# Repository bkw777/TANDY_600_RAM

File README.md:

# SRAM modules for TANDY 600

There are several versions to choose from. They all work the same. Just pick whichever you like based on size, cost of parts, ease of soldering, ease of installing, etc.

[Surface-Mount single-bank 96K](#standard-version) easy to solder, polarity keyed, more expensive  
[Through-Hole single-bank 96K](#through-hole-version) same as above, plus socketable/removable chips  
[Tiny single-bank 96K](#tiny-version) more difficult to solder, miniaturized mostly just as a stunt  
[Tiny dual-bank 192K](#dual-version) most practical way to get all 192K if you can manage the soldering

## Standard Version  
<!-- [PCB from OSHPark](https://oshpark.com/shared_projects/nBVWvJ2W)  -->
[PCB for STANDARD version from PCBWAY](https://www.pcbway.com/project/shareproject/TANDY_600_RAM.html)  
[BOM for STANDARD version from DigiKey](https://www.digikey.com/short/mjtb7rnn)

<!-- [Gerbers](../../releases/latest) -->

----

## Through-Hole Version  

Same schematic as the standard version, just with all through-hole components.  
The ICs may be socketed or not as you wish. When installed in the 600 there is room for both IC's on both boards to be socketed, and the BOM includes sockets.  

[PCB for THROUGH-HOLE version from PCBWAY](https://www.pcbway.com/project/shareproject/TANDY_600_RAM_96K_THT_70a7bb4c.html)  
[BOM for THROUGH-HOLE version from DigiKey](https://www.digikey.com/short/5q7bmv0q)

----

## Tiny Version

[PCB for TINY version from PCBWAY](https://www.pcbway.com/project/shareproject/TANDY_600_RAM_TINY_Version_dedc5289.html)  
[BOM for TINY version from DigiKey](https://www.digikey.com/short/p907n2hq)

----

## DUAL VERSION

Single board that plugs into both CN1 and CN2 and supplies all 192K at once.  

<!-- [PCB from OSHPark]()  -->
[PCB for DUAL version from PCBWAY](https://www.pcbway.com/project/shareproject/TANDY_600_192K_DUAL_RAM_96d16a20.html)  
[BOM for DUAL version from DigiKey](https://www.digikey.com/short/h8bpf4wj)

----

# History / Credits

In 2017 I asked on the Tandy Color Computer Facebook group [if anyone could clone a 96K ram board for Model 600](https://www.facebook.com/groups/2359462640/permalink/10154864662292641/), and Jayeson Lee-Steere produced [Model600Sram_v1.1](https://github.com/bkw777/TANDY_600_RAM/tree/JLS-1.1) and placed it in the public domain.  

This version is different now but started from that.

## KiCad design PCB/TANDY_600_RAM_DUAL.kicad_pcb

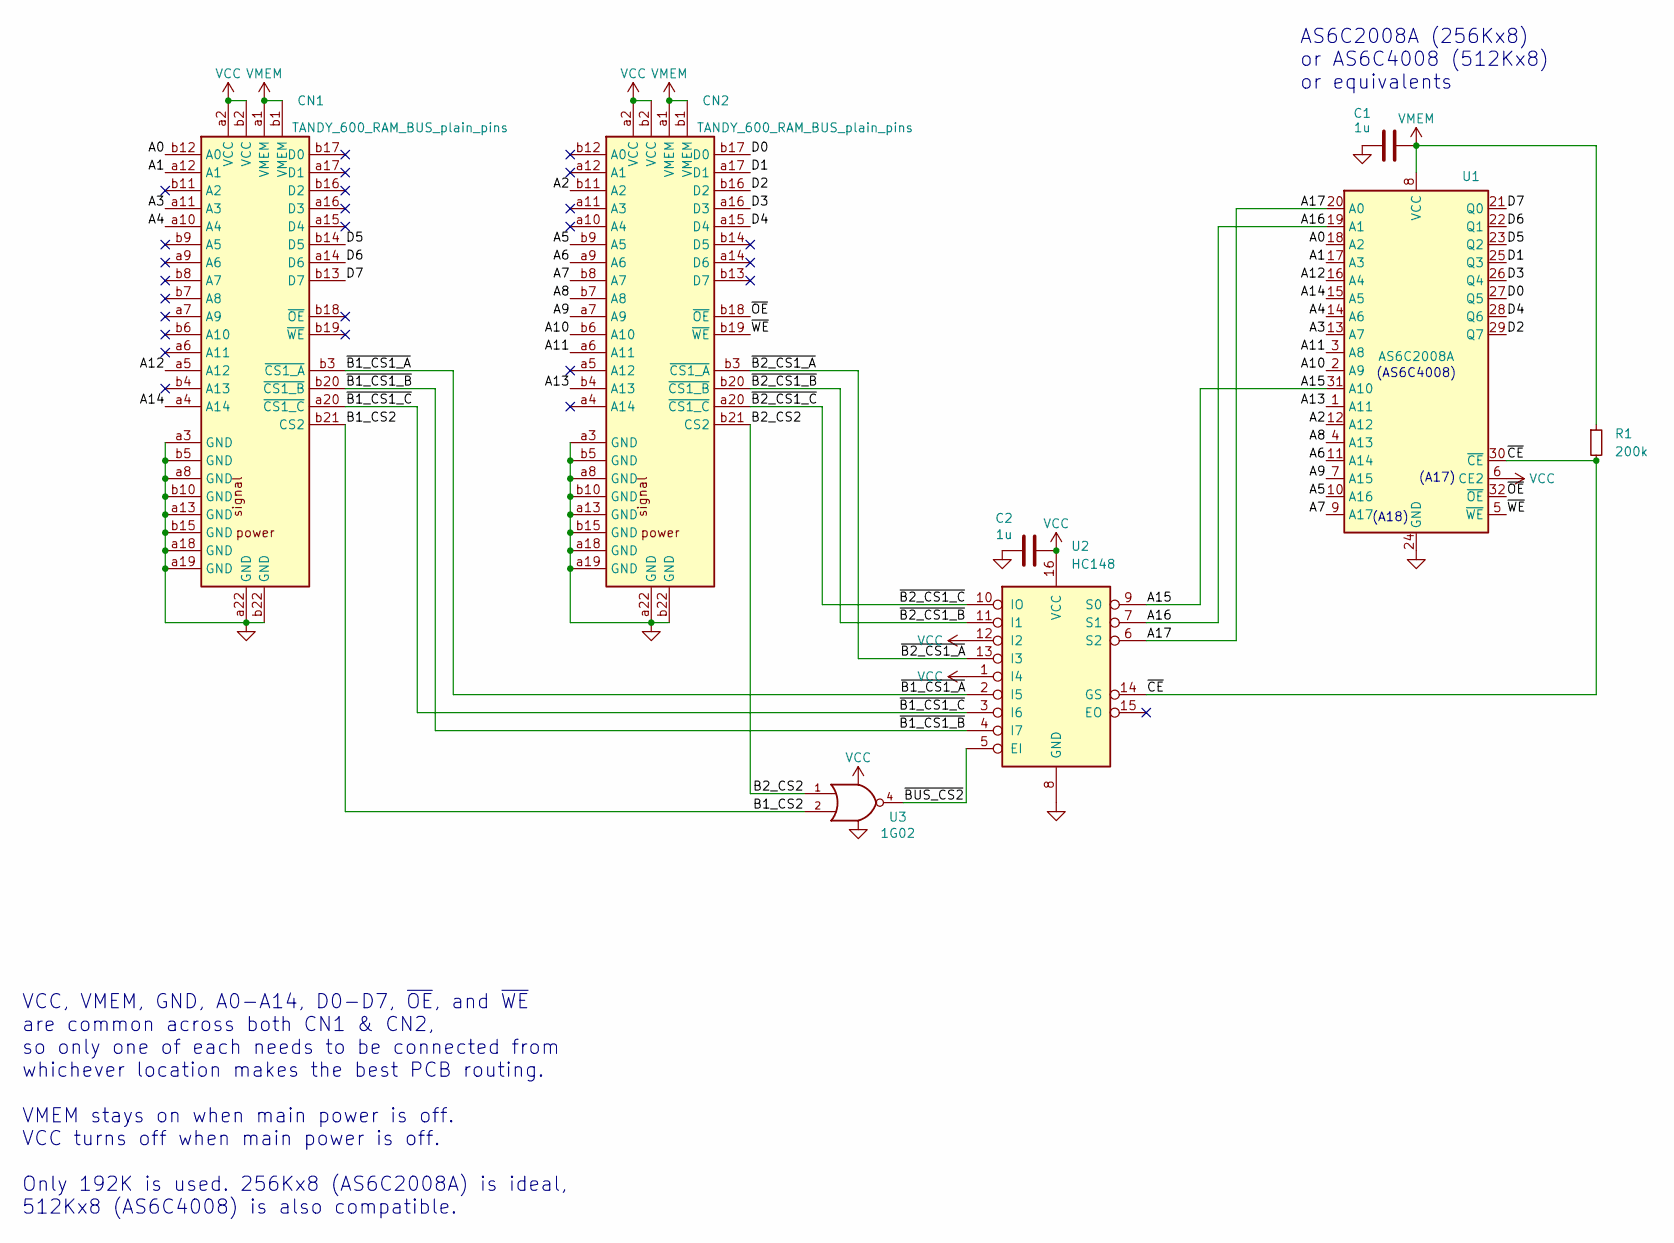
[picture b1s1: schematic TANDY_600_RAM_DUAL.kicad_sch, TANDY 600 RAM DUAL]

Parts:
C1, C2: 1u; C_0805; MPN CL21B105KAFNNNE
CN1, CN2: TANDY_600_RAM_BUS_plain_pins; DIN-41612_02x22_male_vertical_bare_pins; MPN PRPC022DAAN-RC
R1: 200k; R_0805; MPN RMCF0805FT200K
U1: AS6C2008A; TSOP32-dual; MPN AS6C4008-55STIN
U2: HC148; SOIC-16_3.9x9.9mm_P1.27mm; MPN SN74HC148DR
U3: 1G02; SOT-353_SC-70-5; MPN SN74AHC1G02DCKR

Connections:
/A0: CN1.b12 (A0), U1.18 (A2)
/A1: CN1.a12 (A1), U1.17 (A3)
/A2: CN2.b11 (A2), U1.12 (A12)
/A3: CN1.a11 (A3), U1.13 (A7)
/A4: CN1.a10 (A4), U1.14 (A6)
/A5: CN2.b9 (A5), U1.10 (A16)
/A6: CN2.a9 (A6), U1.11 (A14)
/A7: CN2.b8 (A7), U1.9 (A17)
/A8: CN2.b7 (A8), U1.4 (A13)
/A9: CN2.a7 (A9), U1.7 (A15)
/A10: CN2.b6 (A10), U1.2 (A9)
/A11: CN2.a6 (A11), U1.3 (A8)
/A12: CN1.a5 (A12), U1.16 (A4)
/A13: CN2.b4 (A13), U1.1 (A11)
/A14: CN1.a4 (A14), U1.15 (A5)
/A15: U1.31 (A10), U2.9 (S0)
/A16: U1.19 (A1), U2.7 (S1)
/A17: U1.20 (A0), U2.6 (S2)
/B1_CS2: CN1.b21 (CS2), U3.2
/B2_CS2: CN2.b21 (CS2), U3.1
/D0: CN2.b17 (D0), U1.27 (Q5)
/D1: CN2.a17 (D1), U1.25 (Q3)
/D2: CN2.b16 (D2), U1.29 (Q7)
/D3: CN2.a16 (D3), U1.26 (Q4)
/D4: CN2.a15 (D4), U1.28 (Q6)
/D5: CN1.b14 (D5), U1.23 (Q2)
/D6: CN1.a14 (D6), U1.22 (Q1)
/D7: CN1.b13 (D7), U1.21 (Q0)
/~B1_CS1_A: CN1.b3 (~CS1_A), U2.2 (I5)
/~B1_CS1_B: CN1.b20 (~CS1_B), U2.4 (I7)
/~B1_CS1_C: CN1.a20 (~CS1_C), U2.3 (I6)
/~B2_CS1_A: CN2.b3 (~CS1_A), U2.13 (I3)
/~B2_CS1_B: CN2.b20 (~CS1_B), U2.11 (I1)
/~B2_CS1_C: CN2.a20 (~CS1_C), U2.10 (IO)
/~BUS_CS2: U2.5 (EI), U3.4
/~CE: R1.2, U1.30 (~CE), U2.14 (GS)
/~OE: CN2.b18 (~OE), U1.32 (~OE)
/~WE: CN2.b19 (~WE), U1.5 (~WE)
GND: C1.2, C2.2, CN1.a3 (GND), CN1.a8 (GND), CN1.a13 (GND), CN1.a18 (GND), CN1.a19 (GND), CN1.a22 (GND), CN1.b5 (GND), CN1.b10 (GND), CN1.b15 (GND), CN1.b22 (GND), CN2.a3 (GND), CN2.a8 (GND), CN2.a13 (GND), CN2.a18 (GND), CN2.a19 (GND), CN2.a22 (GND), CN2.b5 (GND), CN2.b10 (GND), CN2.b15 (GND), CN2.b22 (GND), U1.24 (GND), U2.8 (GND), U3.3 (GND)
VCC: C2.1, CN1.a2 (VCC), CN1.b2 (VCC), CN2.a2 (VCC), CN2.b2 (VCC), U1.6 (CE2), U2.1 (I4), U2.12 (I2), U2.16 (VCC), U3.5 (VCC)
VMEM: C1.1, CN1.a1 (VMEM), CN1.b1 (VMEM), CN2.a1 (VMEM), CN2.b1 (VMEM), R1.1, U1.8 (VCC)

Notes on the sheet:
(A17)
VCC, VMEM, GND, A0-A14, D0-D7, ~{OE}, and ~{WE} are common across both CN1 & CN2, so only one of each needs to be connected from whichever location makes the best PCB routing. VMEM stays on when main power is off. VCC turns off when main power is off. Only 192K is used. 256Kx8 (AS6C2008A) is ideal,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
AS6C2008A (256Kx8) or AS6C4008 (512Kx8) or equivalents
(A18)
(AS6C4008)

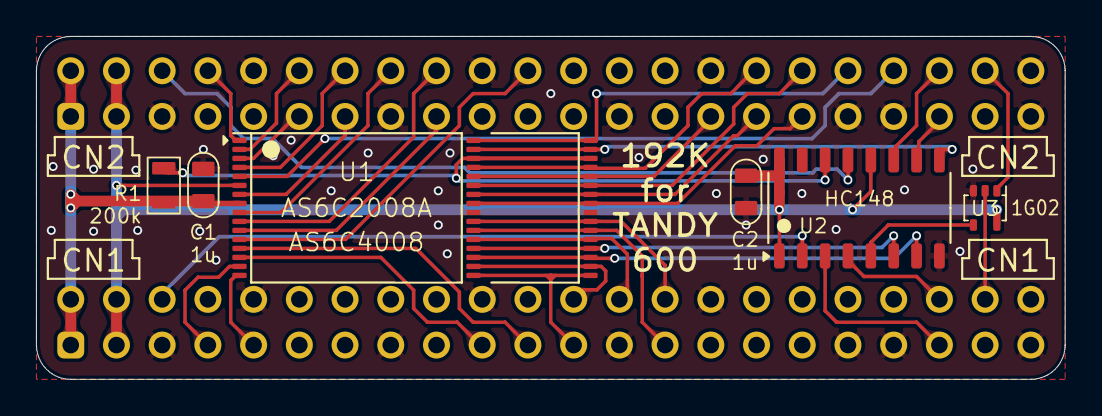
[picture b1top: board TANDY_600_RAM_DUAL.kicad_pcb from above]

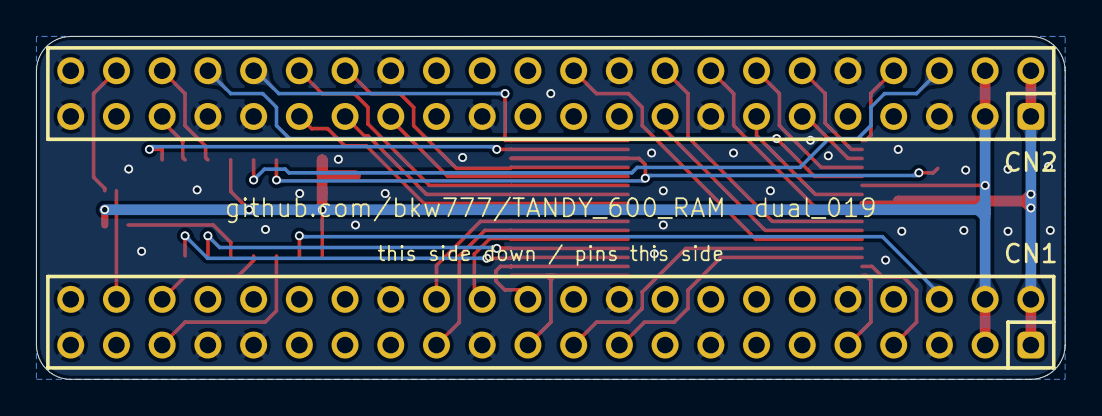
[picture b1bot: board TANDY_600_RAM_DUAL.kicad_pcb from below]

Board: 2 copper layers, 57.2 x 19.1 mm, 8 parts (2 on the bottom side), 41 nets.

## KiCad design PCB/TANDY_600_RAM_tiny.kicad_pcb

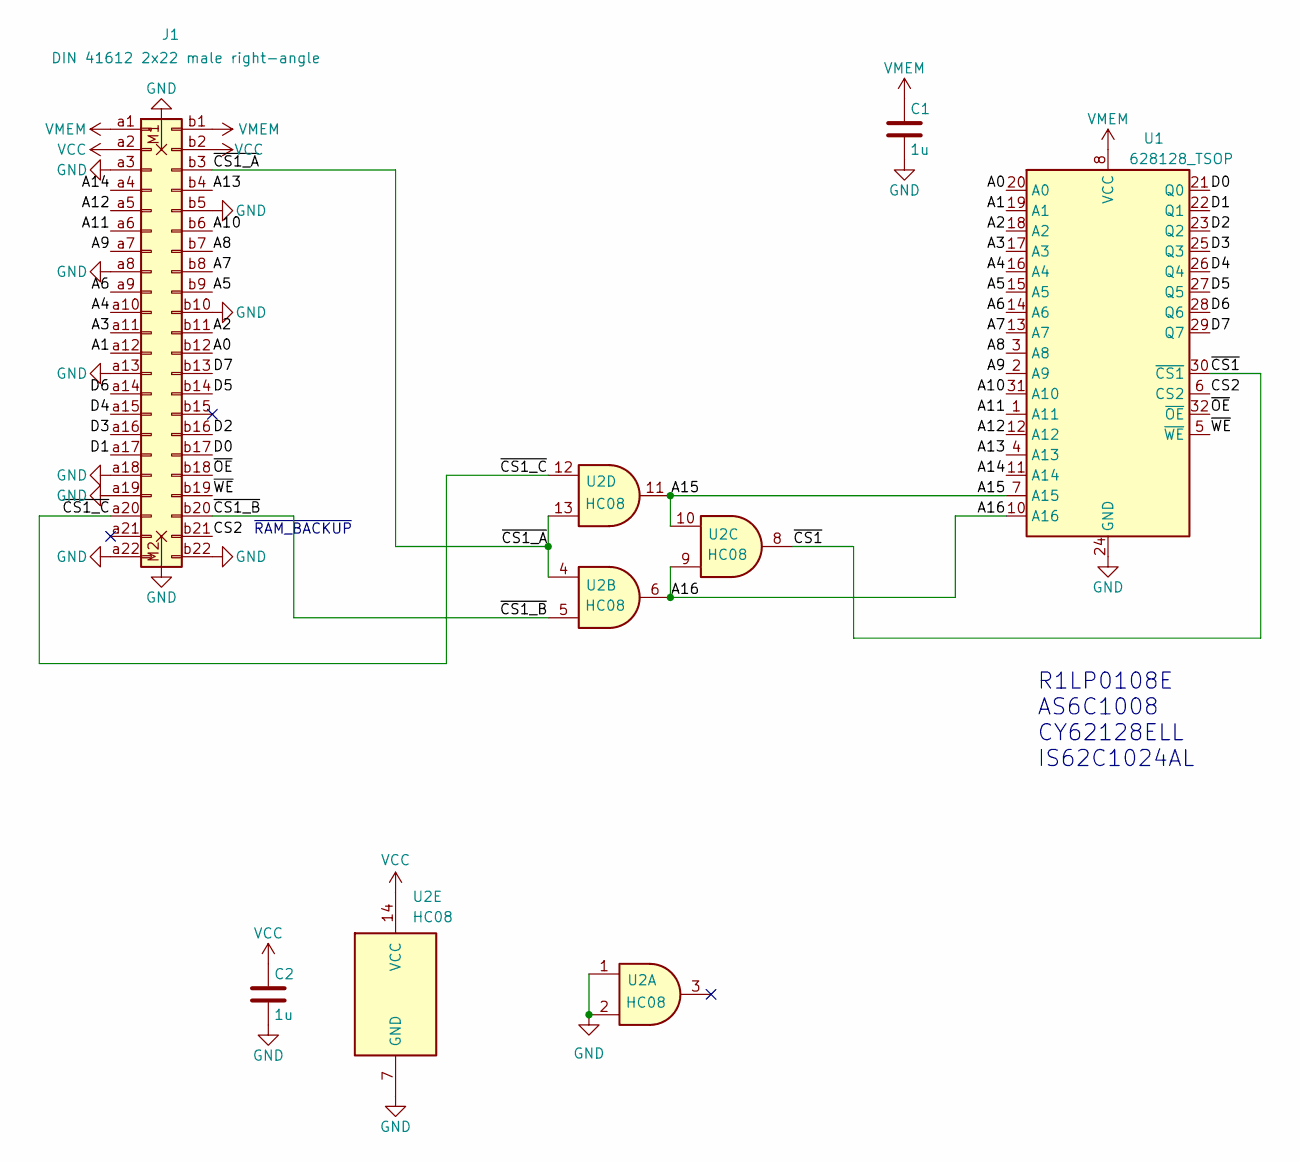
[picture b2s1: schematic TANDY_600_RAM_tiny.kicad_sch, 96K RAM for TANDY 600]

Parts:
C1, C2: 1u; C_0805
J1: DIN 41612 2x22 male right-angle; DIN-41612_02x22_male_horizontal
U1: 628128_TSOP; TSOP32-dual
U2: HC08; TSSOP-14_4.4x5mm_P0.65mm

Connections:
/A0: J1.b12, U1.20 (A0)
/A1: J1.a12, U1.19 (A1)
/A2: J1.b11, U1.18 (A2)
/A3: J1.a11, U1.17 (A3)
/A4: J1.a10, U1.16 (A4)
/A5: J1.b9, U1.15 (A5)
/A6: J1.a9, U1.14 (A6)
/A7: J1.b8, U1.13 (A7)
/A8: J1.b7, U1.3 (A8)
/A9: J1.a7, U1.2 (A9)
/A10: J1.b6, U1.31 (A10)
/A11: J1.a6, U1.1 (A11)
/A12: J1.a5, U1.12 (A12)
/A13: J1.b4, U1.4 (A13)
/A14: J1.a4, U1.11 (A14)
/A15: U1.7 (A15), U2.10, U2.11
/A16: U1.10 (A16), U2.6, U2.9
/CS2: J1.b21, U1.6 (CS2)
/D0: J1.b17, U1.21 (Q0)
/D1: J1.a17, U1.22 (Q1)
/D2: J1.b16, U1.23 (Q2)
/D3: J1.a16, U1.25 (Q3)
/D4: J1.a15, U1.26 (Q4)
/D5: J1.b14, U1.27 (Q5)
/D6: J1.a14, U1.28 (Q6)
/D7: J1.b13, U1.29 (Q7)
/~CS1_A: J1.b3, U2.4, U2.13
/~CS1_B: J1.b20, U2.5
/~CS1_C: J1.a20, U2.12
/~CS1: U1.30 (~CS1), U2.8
/~OE: J1.b18, U1.32 (~OE)
/~WE: J1.b19, U1.5 (~WE)
GND: C1.2, C2.2, J1.M1 (mount), J1.M2 (mount), J1.a3, J1.a8, J1.a13, J1.a18, J1.a19, J1.a22, J1.b5, J1.b10, J1.b22, U1.24 (GND), U2.1, U2.2, U2.7 (GND)
VCC: C2.1, J1.a2, J1.b2, U2.14 (VCC)
VMEM: C1.1, J1.a1, J1.b1, U1.8 (VCC)

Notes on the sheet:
~{RAM_BACKUP}
R1LP0108E AS6C1008 CY62128ELL IS62C1024AL

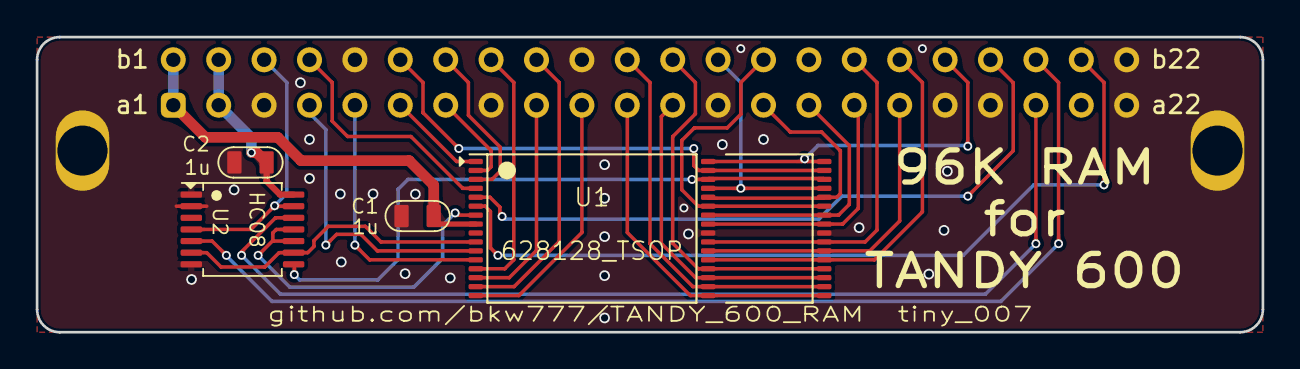
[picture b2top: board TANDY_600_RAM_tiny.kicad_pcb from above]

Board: 2 copper layers, 68.6 x 16.5 mm, 5 parts (1 on the bottom side), 35 nets.

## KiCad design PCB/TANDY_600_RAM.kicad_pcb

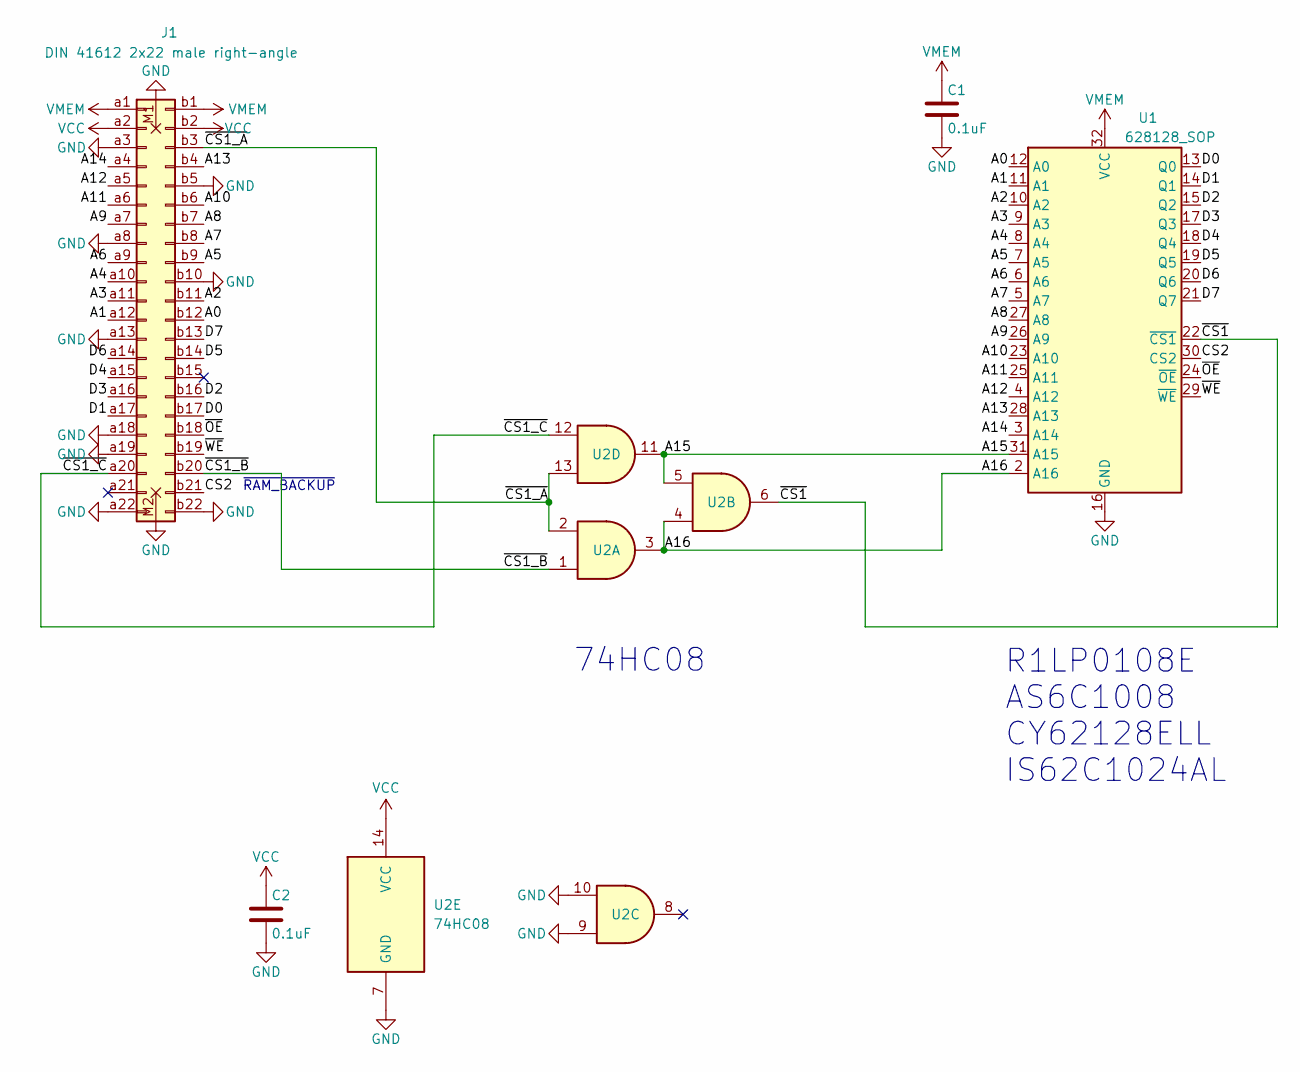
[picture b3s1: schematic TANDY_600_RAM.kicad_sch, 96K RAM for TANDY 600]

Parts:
C1, C2: 0.1uF; C_1206
J1: DIN 41612 2x22 male right-angle; DIN-41612_02x22_male_horizontal
U1: 628128_SOP; SOP-32W
U2: 74HC08; SOIC-14_3.9x8.7mm_P1.27mm

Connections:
/A0: J1.b12, U1.12 (A0)
/A1: J1.a12, U1.11 (A1)
/A2: J1.b11, U1.10 (A2)
/A3: J1.a11, U1.9 (A3)
/A4: J1.a10, U1.8 (A4)
/A5: J1.b9, U1.7 (A5)
/A6: J1.a9, U1.6 (A6)
/A7: J1.b8, U1.5 (A7)
/A8: J1.b7, U1.27 (A8)
/A9: J1.a7, U1.26 (A9)
/A10: J1.b6, U1.23 (A10)
/A11: J1.a6, U1.25 (A11)
/A12: J1.a5, U1.4 (A12)
/A13: J1.b4, U1.28 (A13)
/A14: J1.a4, U1.3 (A14)
/A15: U1.31 (A15), U2.5, U2.11
/A16: U1.2 (A16), U2.3, U2.4
/CS2: J1.b21, U1.30 (CS2)
/D0: J1.b17, U1.13 (Q0)
/D1: J1.a17, U1.14 (Q1)
/D2: J1.b16, U1.15 (Q2)
/D3: J1.a16, U1.17 (Q3)
/D4: J1.a15, U1.18 (Q4)
/D5: J1.b14, U1.19 (Q5)
/D6: J1.a14, U1.20 (Q6)
/D7: J1.b13, U1.21 (Q7)
/~CS1_A: J1.b3, U2.2, U2.13
/~CS1_B: J1.b20, U2.1
/~CS1_C: J1.a20, U2.12
/~CS1: U1.22 (~CS1), U2.6
/~OE: J1.b18, U1.24 (~OE)
/~WE: J1.b19, U1.29 (~WE)
GND: C1.2, C2.2, J1.M1 (mount), J1.M2 (mount), J1.a3, J1.a8, J1.a13, J1.a18, J1.a19, J1.a22, J1.b5, J1.b10, J1.b22, U1.16 (GND), U2.7 (GND), U2.9, U2.10
VCC: C2.1, J1.a2, J1.b2, U2.14 (VCC)
VMEM: C1.1, J1.a1, J1.b1, U1.32 (VCC)

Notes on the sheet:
~{RAM_BACKUP}
R1LP0108E AS6C1008 CY62128ELL IS62C1024AL
74HC08

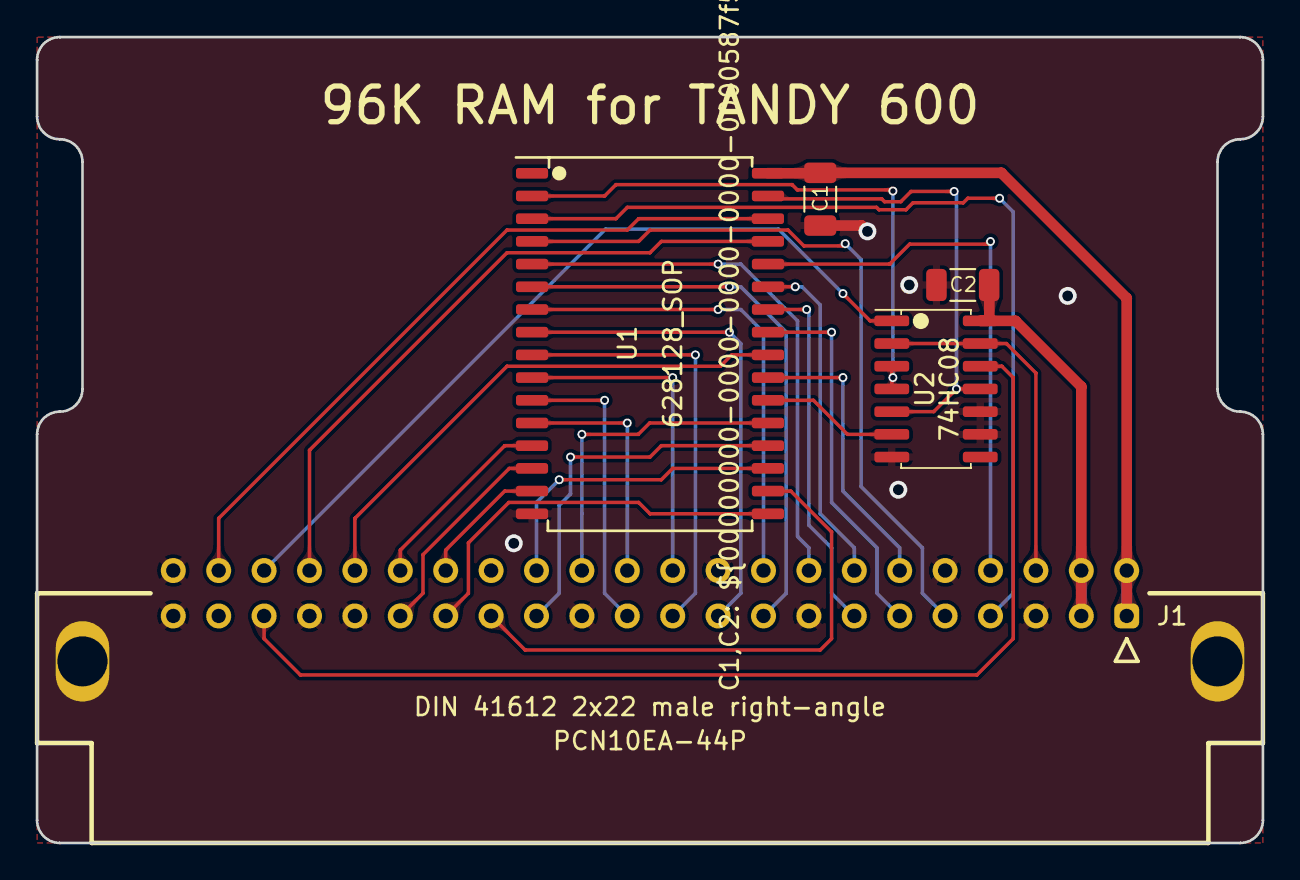
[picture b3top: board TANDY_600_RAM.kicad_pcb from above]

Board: 2 copper layers, 68.6 x 45.1 mm, 5 parts (0 on the bottom side), 35 nets.

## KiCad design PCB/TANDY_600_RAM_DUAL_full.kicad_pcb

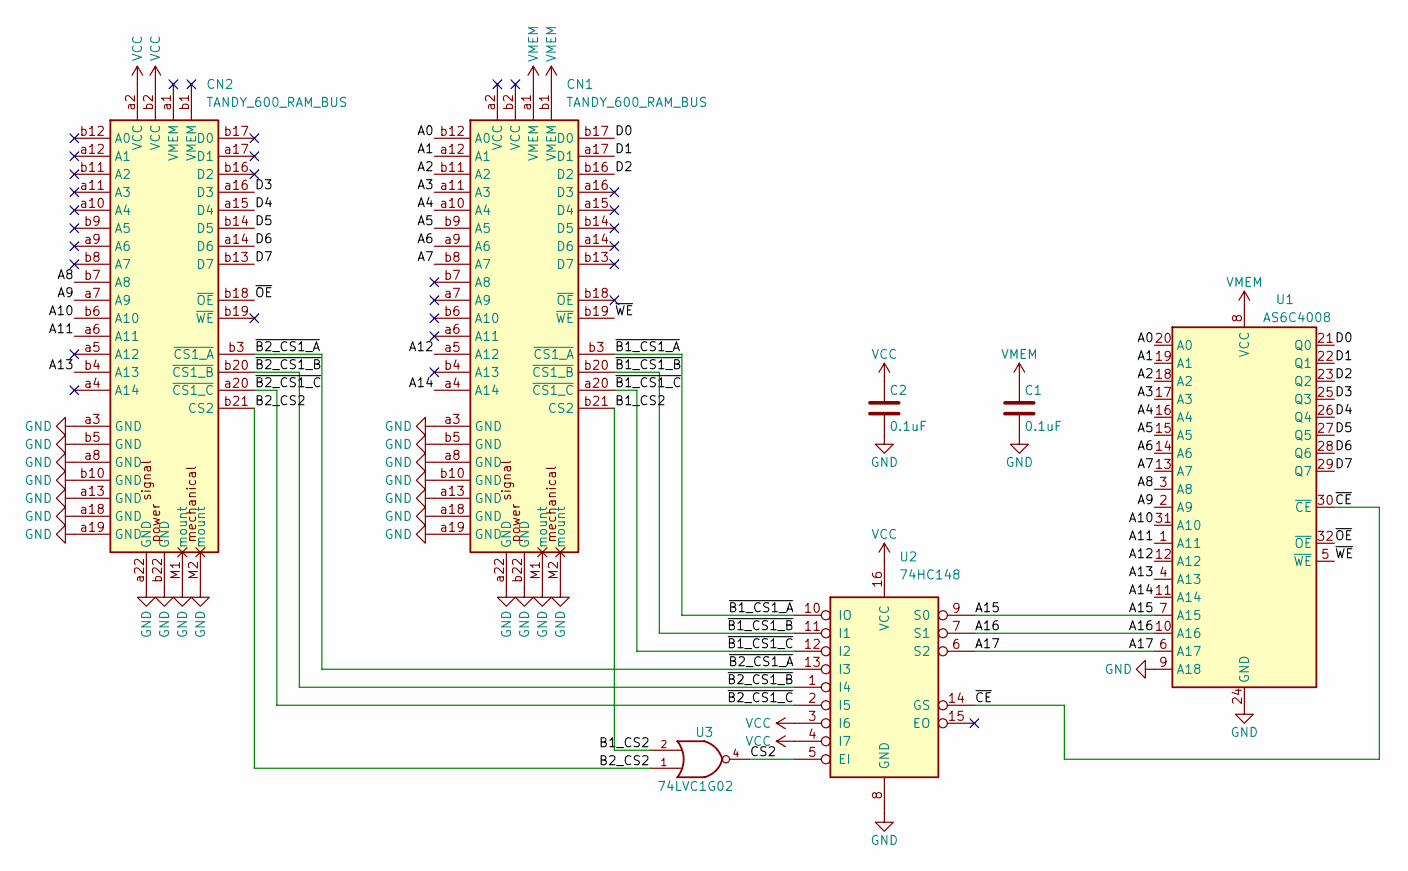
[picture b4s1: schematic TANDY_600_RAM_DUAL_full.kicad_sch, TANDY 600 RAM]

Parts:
C1, C2: 0.1uF; C_0805
CN1, CN2: TANDY_600_RAM_BUS; DIN-41612_02x22_male_vertical
U1: AS6C4008; TSOP32-dual
U2: 74HC148; SOIC-16_4x10
U3: 74LVC1G02; SOT-353_SC-70-5

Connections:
/A0: CN1.b12 (A0), U1.20 (A0)
/A1: CN1.a12 (A1), U1.19 (A1)
/A2: CN1.b11 (A2), U1.18 (A2)
/A3: CN1.a11 (A3), U1.17 (A3)
/A4: CN1.a10 (A4), U1.16 (A4)
/A5: CN1.b9 (A5), U1.15 (A5)
/A6: CN1.a9 (A6), U1.14 (A6)
/A7: CN1.b8 (A7), U1.13 (A7)
/A8: CN2.b7 (A8), U1.3 (A8)
/A9: CN2.a7 (A9), U1.2 (A9)
/A10: CN2.b6 (A10), U1.31 (A10)
/A11: CN2.a6 (A11), U1.1 (A11)
/A12: CN1.a5 (A12), U1.12 (A12)
/A13: CN2.b4 (A13), U1.4 (A13)
/A14: CN1.a4 (A14), U1.11 (A14)
/A15: U1.7 (A15), U2.9 (S0)
/A16: U1.10 (A16), U2.7 (S1)
/A17: U1.6 (A17), U2.6 (S2)
/B1_CS2: CN1.b21 (CS2), U3.2
/B2_CS2: CN2.b21 (CS2), U3.1
/CS2: U2.5 (EI), U3.4
/D0: CN1.b17 (D0), U1.21 (Q0)
/D1: CN1.a17 (D1), U1.22 (Q1)
/D2: CN1.b16 (D2), U1.23 (Q2)
/D3: CN2.a16 (D3), U1.25 (Q3)
/D4: CN2.a15 (D4), U1.26 (Q4)
/D5: CN2.b14 (D5), U1.27 (Q5)
/D6: CN2.a14 (D6), U1.28 (Q6)
/D7: CN2.b13 (D7), U1.29 (Q7)
/~B1_CS1_A: CN1.b3 (~CS1_A), U2.10 (IO)
/~B1_CS1_B: CN1.b20 (~CS1_B), U2.11 (I1)
/~B1_CS1_C: CN1.a20 (~CS1_C), U2.12 (I2)
/~B2_CS1_A: CN2.b3 (~CS1_A), U2.13 (I3)
/~B2_CS1_B: CN2.b20 (~CS1_B), U2.1 (I4)
/~B2_CS1_C: CN2.a20 (~CS1_C), U2.2 (I5)
/~CE: U1.30 (~CE), U2.14 (GS)
/~OE: CN2.b18 (~OE), U1.32 (~OE)
/~WE: CN1.b19 (~WE), U1.5 (~WE)
GND: C1.2, C2.2, CN1.M1 (mount), CN1.M2 (mount), CN1.a3 (GND), CN1.a8 (GND), CN1.a13 (GND), CN1.a18 (GND), CN1.a19 (GND), CN1.a22 (GND), CN1.b5 (GND), CN1.b10 (GND), CN1.b22 (GND), CN2.M1 (mount), CN2.M2 (mount), CN2.a3 (GND), CN2.a8 (GND), CN2.a13 (GND), CN2.a18 (GND), CN2.a19 (GND), CN2.a22 (GND), CN2.b5 (GND), CN2.b10 (GND), CN2.b22 (GND), U1.9 (A18), U1.24 (GND), U2.8 (GND), U3.3 (GND)
VCC: C2.1, CN2.a2 (VCC), CN2.b2 (VCC), U2.3 (I6), U2.4 (I7), U2.16 (VCC), U3.5 (VCC)
VMEM: C1.1, CN1.a1 (VMEM), CN1.b1 (VMEM), U1.8 (VCC)

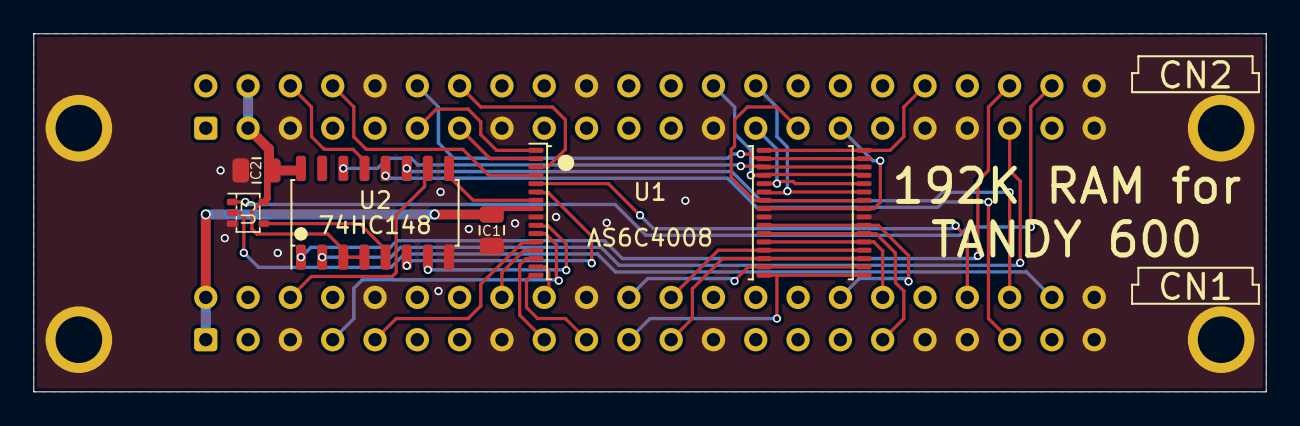
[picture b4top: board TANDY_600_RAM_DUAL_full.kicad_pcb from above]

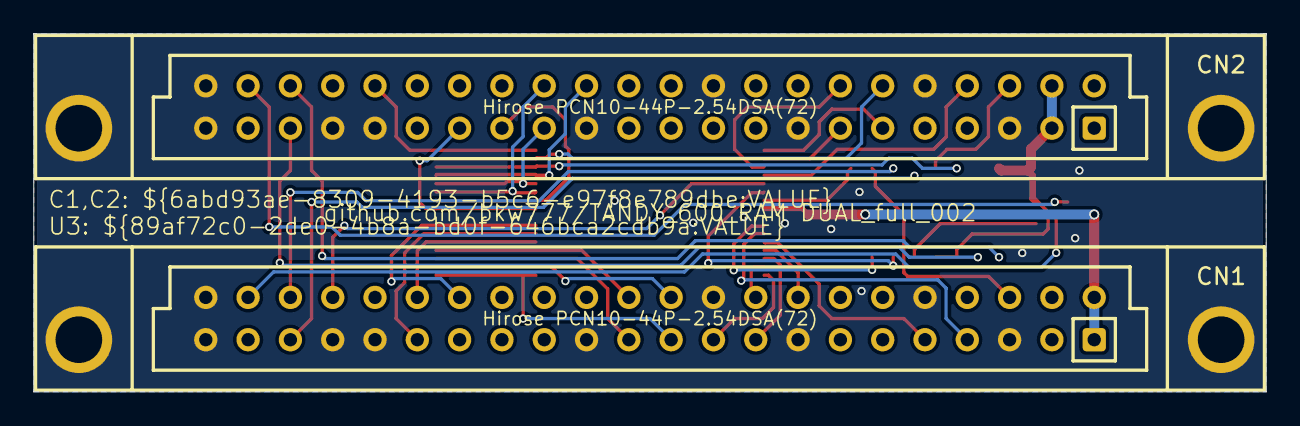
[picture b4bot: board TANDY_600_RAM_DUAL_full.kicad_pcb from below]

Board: 2 copper layers, 74.0 x 21.5 mm, 7 parts (2 on the bottom side), 41 nets.

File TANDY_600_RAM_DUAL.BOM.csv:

"Index","Quantity","Part Number","Manufacturer Part Number","Description","Customer Reference","Available","Backorder","Unit Price","Extended Price USD"
"1","1","296-26468-1-ND","SN74HC148DR","IC PRIORITY ENCOD 1 X 8:3 16SOIC","","1","0","0.44000","0.44"
"2","1","1450-1029-ND","AS6C4008-55STIN","IC SRAM 4MBIT PARALLEL 32STSOP","","1","0","5.16000","5.16"
"3","1","1727-6062-1-ND","74LVC1G02GW,125","IC GATE NOR 1CH 2-INP 5TSSOP","","1","0","0.38000","0.38"
"4","2","478-12795-1-ND","KGM21NR71C104MT","CAP CER 0.1UF 16V X7R 0805","","2","0","0.23000","0.46"
"5","2","S2011EC-22-ND","PRPC022DAAN-RC","CONN HEADER VERT 44POS 2.54MM","","2","0","0.82000","1.64"
"6","1","RMCF0805JT200KCT-ND","RMCF0805JT200K","RES 200K OHM 5% 1/8W 0805","","1","0","0.10000","0.10"

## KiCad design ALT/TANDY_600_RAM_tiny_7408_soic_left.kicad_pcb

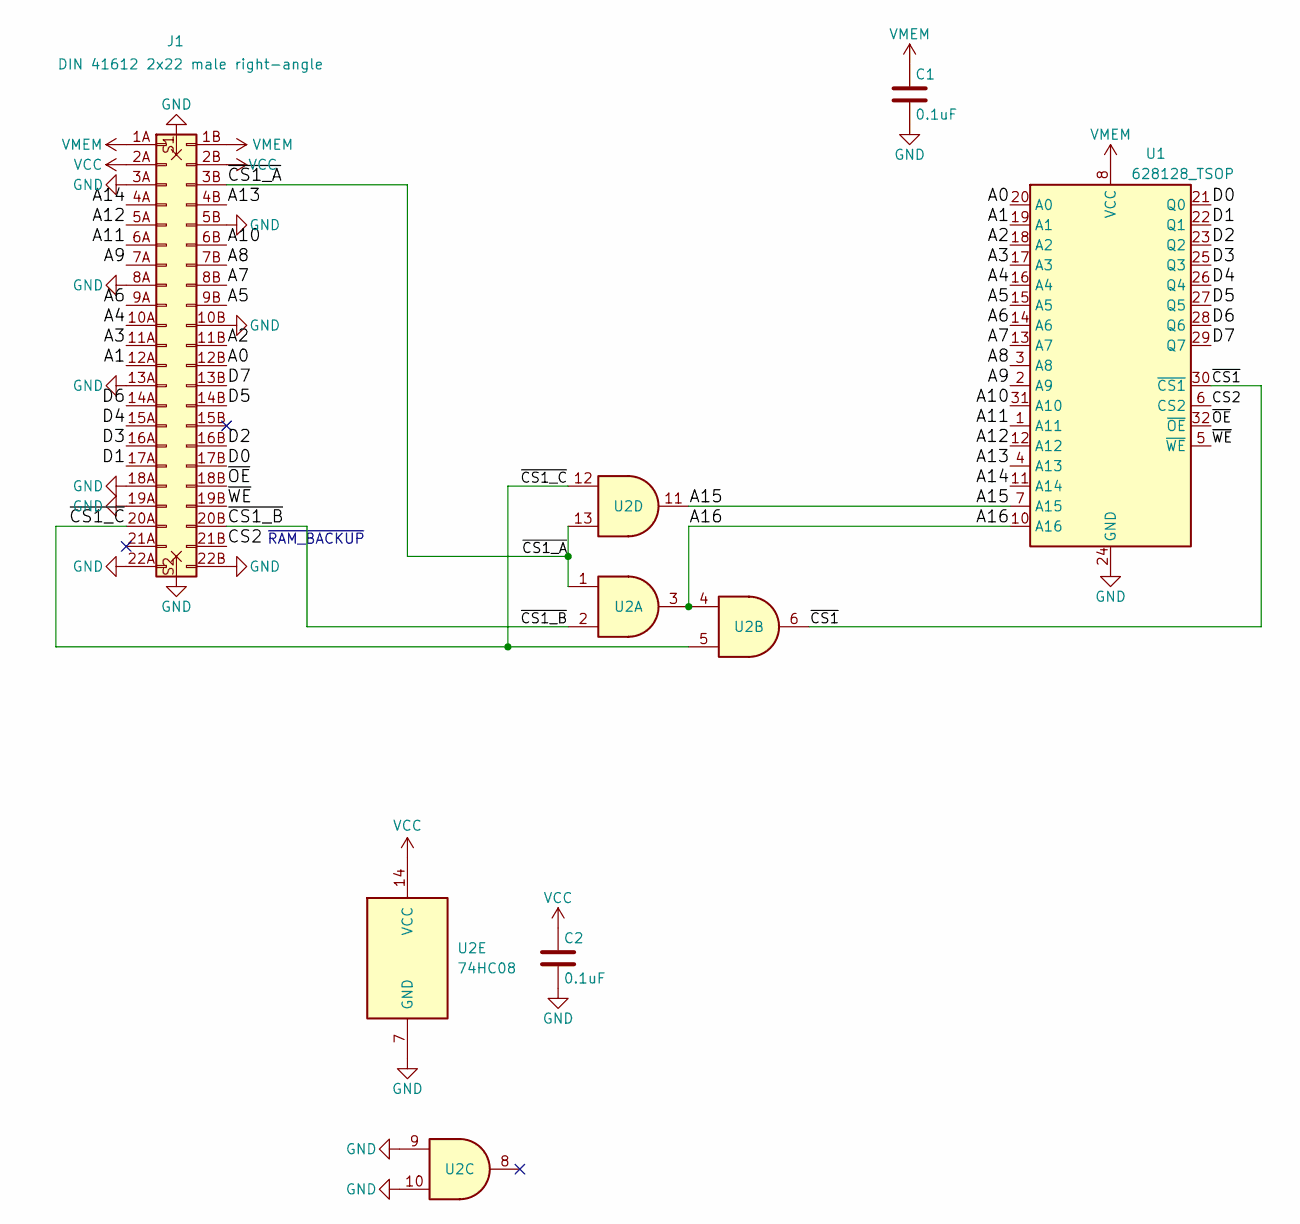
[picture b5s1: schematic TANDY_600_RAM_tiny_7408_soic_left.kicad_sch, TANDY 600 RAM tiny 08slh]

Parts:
C1, C2: 0.1uF; C_0805
J1: DIN 41612 2x22 male right-angle
U1: 628128_TSOP; TSOP32-dual
U2: 74HC08; SOIC-14_3.9x8.7mm_P1.27mm

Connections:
/A0: J1.12B, U1.20 (A0)
/A1: J1.12A, U1.19 (A1)
/A2: J1.11B, U1.18 (A2)
/A3: J1.11A, U1.17 (A3)
/A4: J1.10A, U1.16 (A4)
/A5: J1.9B, U1.15 (A5)
/A6: J1.9A, U1.14 (A6)
/A7: J1.8B, U1.13 (A7)
/A8: J1.7B, U1.3 (A8)
/A9: J1.7A, U1.2 (A9)
/A10: J1.6B, U1.31 (A10)
/A11: J1.6A, U1.1 (A11)
/A12: J1.5A, U1.12 (A12)
/A13: J1.4B, U1.4 (A13)
/A14: J1.4A, U1.11 (A14)
/A15: U1.7 (A15), U2.11
/A16: U1.10 (A16), U2.3, U2.4
/CS2: J1.21B, U1.6 (CS2)
/D0: J1.17B, U1.21 (Q0)
/D1: J1.17A, U1.22 (Q1)
/D2: J1.16B, U1.23 (Q2)
/D3: J1.16A, U1.25 (Q3)
/D4: J1.15A, U1.26 (Q4)
/D5: J1.14B, U1.27 (Q5)
/D6: J1.14A, U1.28 (Q6)
/D7: J1.13B, U1.29 (Q7)
/~CS1_A: J1.3B, U2.1, U2.13
/~CS1_B: J1.20B, U2.2
/~CS1_C: J1.20A, U2.5, U2.12
/~CS1: U1.30 (~CS1), U2.6
/~OE: J1.18B, U1.32 (~OE)
/~WE: J1.19B, U1.5 (~WE)
GND: C1.2, C2.2, J1.3A, J1.5B, J1.8A, J1.10B, J1.13A, J1.18A, J1.19A, J1.22A, J1.22B, J1.S1 (mount), J1.S2 (mount), U1.24 (GND), U2.7 (GND), U2.9, U2.10
VCC: C2.1, J1.2A, J1.2B, U2.14 (VCC)
VMEM: C1.1, J1.1A, J1.1B, U1.8 (VCC)

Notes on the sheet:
~{RAM_BACKUP}

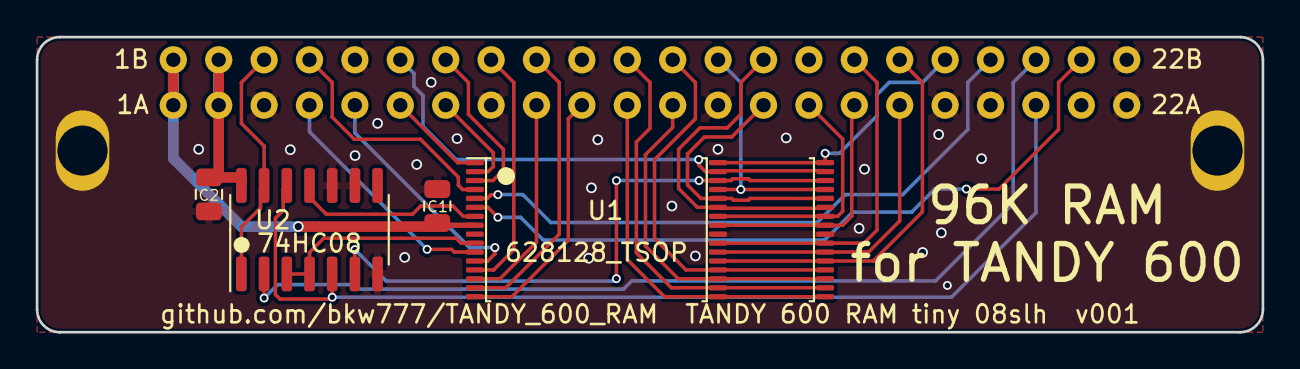
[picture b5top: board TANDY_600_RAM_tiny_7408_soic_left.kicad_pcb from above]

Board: 2 copper layers, 68.6 x 16.5 mm, 5 parts (1 on the bottom side), 35 nets.

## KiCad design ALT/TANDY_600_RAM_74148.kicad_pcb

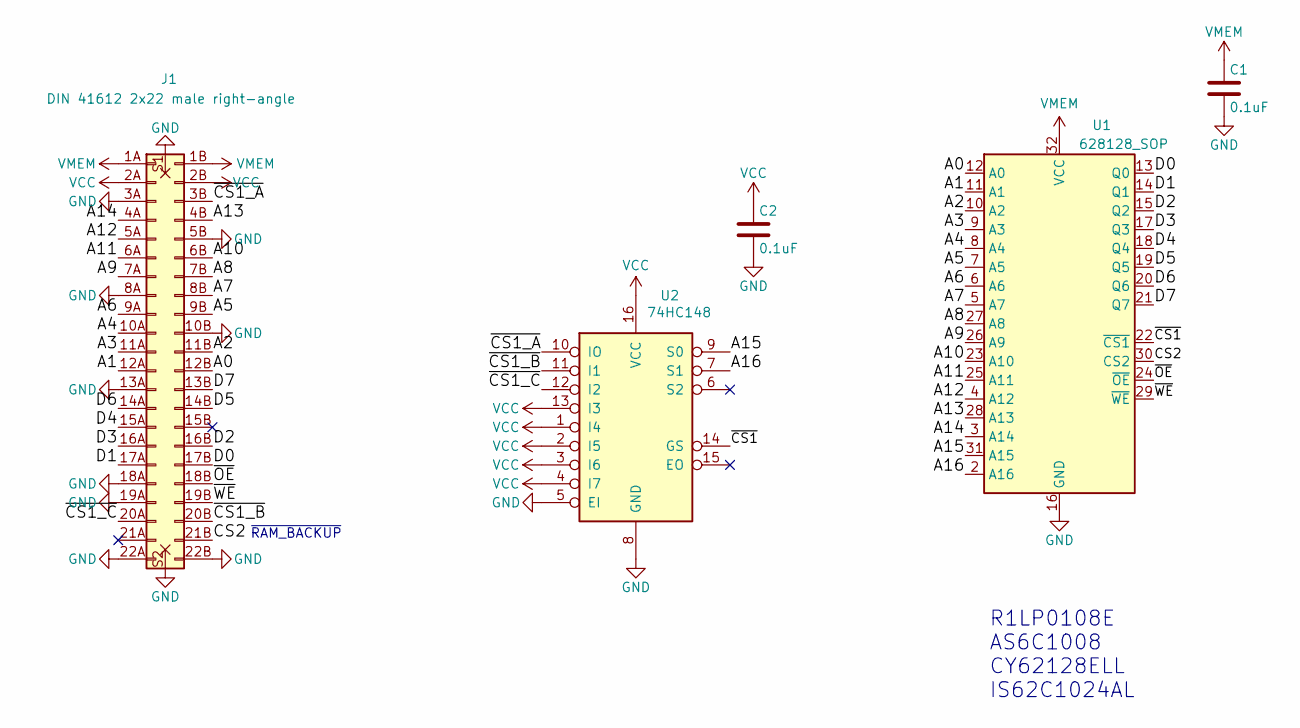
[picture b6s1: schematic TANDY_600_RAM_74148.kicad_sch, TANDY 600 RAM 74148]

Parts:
C1, C2: 0.1uF; C_1206
J1: DIN 41612 2x22 male right-angle
U1: 628128_SOP; SOP-32W
U2: 74HC148; SOIC-SOP-16

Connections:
/A0: J1.12B, U1.12 (A0)
/A1: J1.12A, U1.11 (A1)
/A2: J1.11B, U1.10 (A2)
/A3: J1.11A, U1.9 (A3)
/A4: J1.10A, U1.8 (A4)
/A5: J1.9B, U1.7 (A5)
/A6: J1.9A, U1.6 (A6)
/A7: J1.8B, U1.5 (A7)
/A8: J1.7B, U1.27 (A8)
/A9: J1.7A, U1.26 (A9)
/A10: J1.6B, U1.23 (A10)
/A11: J1.6A, U1.25 (A11)
/A12: J1.5A, U1.4 (A12)
/A13: J1.4B, U1.28 (A13)
/A14: J1.4A, U1.3 (A14)
/A15: U1.31 (A15), U2.9 (S0)
/A16: U1.2 (A16), U2.7 (S1)
/CS2: J1.21B, U1.30 (CS2)
/D0: J1.17B, U1.13 (Q0)
/D1: J1.17A, U1.14 (Q1)
/D2: J1.16B, U1.15 (Q2)
/D3: J1.16A, U1.17 (Q3)
/D4: J1.15A, U1.18 (Q4)
/D5: J1.14B, U1.19 (Q5)
/D6: J1.14A, U1.20 (Q6)
/D7: J1.13B, U1.21 (Q7)
/~CS1_A: J1.3B, U2.10 (IO)
/~CS1_B: J1.20B, U2.11 (I1)
/~CS1_C: J1.20A, U2.12 (I2)
/~CS1: U1.22 (~CS1), U2.14 (GS)
/~OE: J1.18B, U1.24 (~OE)
/~WE: J1.19B, U1.29 (~WE)
GND: C1.2, C2.2, J1.3A, J1.5B, J1.8A, J1.10B, J1.13A, J1.18A, J1.19A, J1.22A, J1.22B, J1.S1 (mount), J1.S2 (mount), U1.16 (GND), U2.5 (EI), U2.8 (GND)
VCC: C2.1, J1.2A, J1.2B, U2.1 (I4), U2.2 (I5), U2.3 (I6), U2.4 (I7), U2.13 (I3), U2.16 (VCC)
VMEM: C1.1, J1.1A, J1.1B, U1.32 (VCC)

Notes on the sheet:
~{RAM_BACKUP}
R1LP0108E AS6C1008 CY62128ELL IS62C1024AL

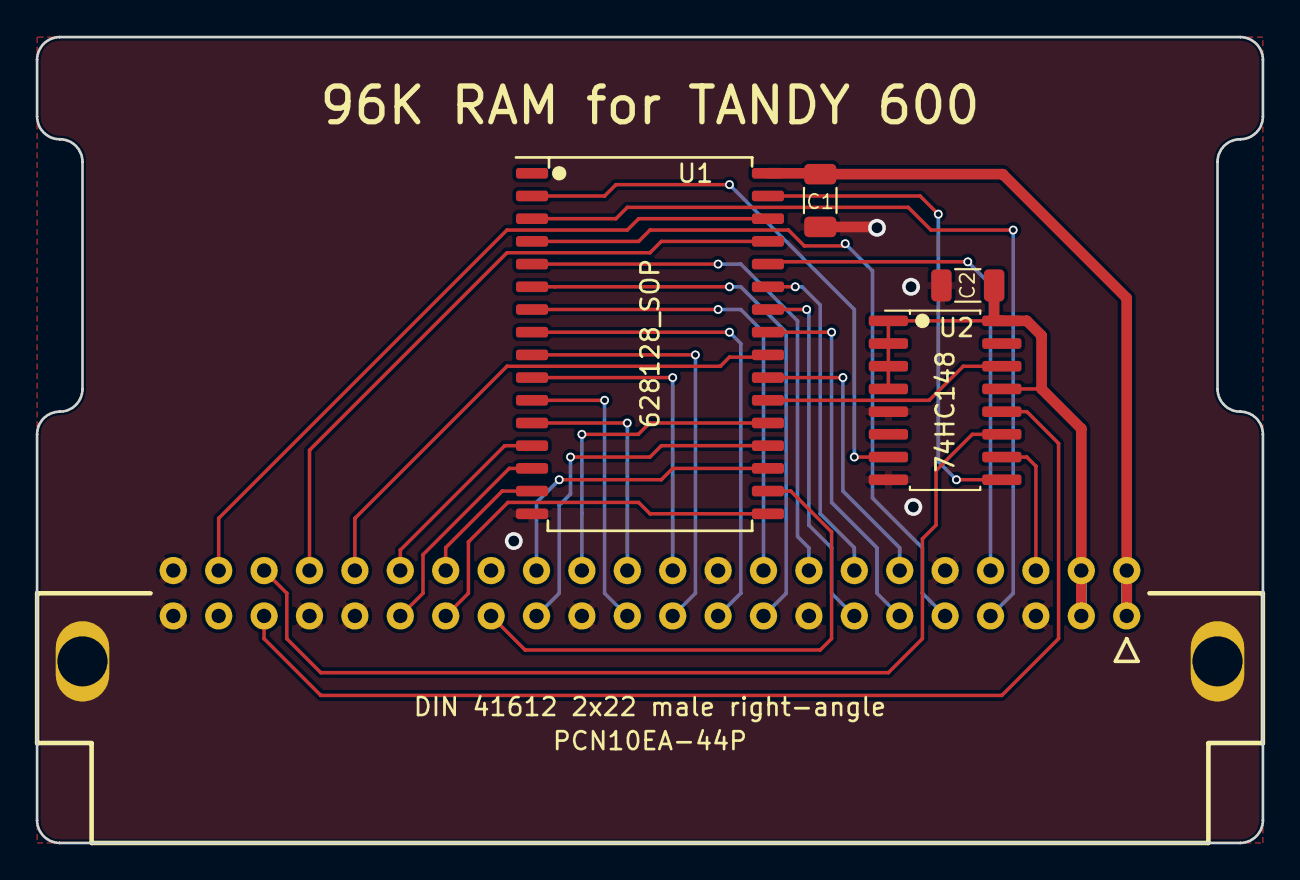
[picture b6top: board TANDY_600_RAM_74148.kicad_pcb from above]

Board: 2 copper layers, 68.6 x 45.1 mm, 5 parts (0 on the bottom side), 35 nets.

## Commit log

2021-08-12 JLS-v1.1 original files plus readme & pics
2021-08-12 re-work into a self-contained project, add 3d models, massage pcb layout
2021-08-12 remove 74HC08
2021-08-12 readme and BOM.csv
2021-08-13 re-order the signal lines so they match from bus to chip
2021-09-03 move chip away from edge, add service manual scans
2021-09-11 support either SOIC or SOP 74HC148
2021-09-28 unscramble cs_a,b,c -> a15,16
2021-10-14 More fathomable pinout on the 74148
2021-10-15 v006.1
2021-10-15 v006.2
2022-09-08 kicad 6
2022-09-08 silkscreen, readme, pics
2022-09-16 datasheets, update bom, teardrops on release gerbers
2022-09-16 missing schematic svg
2022-09-18 schematic plot background
2022-09-18 add tiny version
2022-09-19 silkscreen, symbols, footprints touchups
2022-09-19 pics
2022-09-19 re-visible gnd pins on symbols
2022-09-19 add alternative tiny layout, lengthen tsop footprint slightly
2022-09-27 Replace 74148 circuit with 7408 circuit, add THT version, add several variations in ALT dir.
2022-09-27 tht bom
2022-09-27 tiny bom
2022-09-29 add DUAL version
2022-10-01 wrong sram pinout on dual version
2022-10-01 tht routing
2022-10-04 gnd on tiny, new dual sch, bus connector symbol & footprint
2022-10-13 pics & updated bom for dual version
2022-10-14 pics of new main smt version based on 74hc08
2022-10-14 main version bom
2022-10-20 add full-size dual
2022-10-20 readme typo
2022-10-20 dual full pics
2022-10-29 footprints, ground paths
2022-10-29 pics & pcb link for THT
2022-10-30 undo accidentally saved filleted tracks on THT
2022-11-12 dual_008
2022-12-06 dual bom cart link
2022-12-07 hide the full dual version in readme
2022-12-07 bom links text
2022-12-07 readme bom links
2022-12-22 support 256Kx8 chip on dual
2022-12-22 tested tiny version, add pcbway link
2023-12-10 dual version add /CE pullup for battery life
2023-12-10 dual bom
2024-12-04 footprints on dual
2024-12-04 footprints on tiny
2024-12-08 fix gitignore, add missing datasheets dir
2024-12-09 rename 3d dir to 3dshapes to standardize
2024-12-20 dual: sch add MPNs & bom, pcb move A14,16,17
2024-12-21 dual: relocate chips for shorter traces & fewer vias, add service manual
2024-12-21 dual: sch revision
2025-10-29 datasheets OPRM pinout

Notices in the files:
ALT/TANDY_600_RAM_74148.kicad_pcb:
LICENSE: CC-BY-SA 4.0
PCB/TANDY_600_RAM.kicad_sch:
CC-BY-SA
